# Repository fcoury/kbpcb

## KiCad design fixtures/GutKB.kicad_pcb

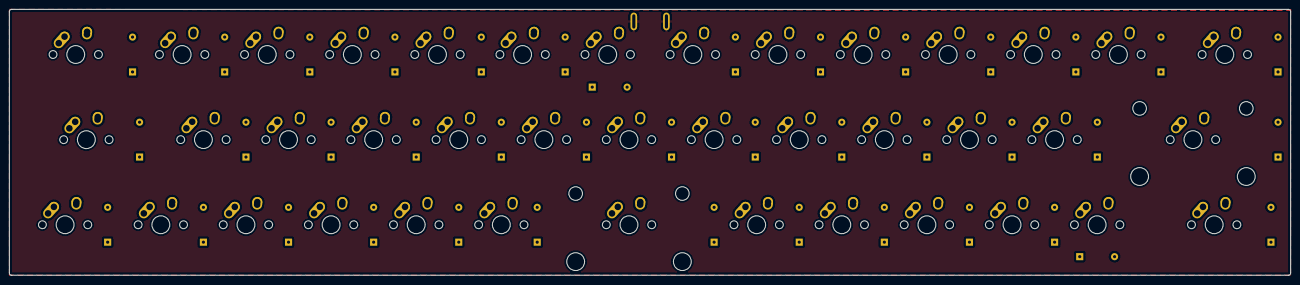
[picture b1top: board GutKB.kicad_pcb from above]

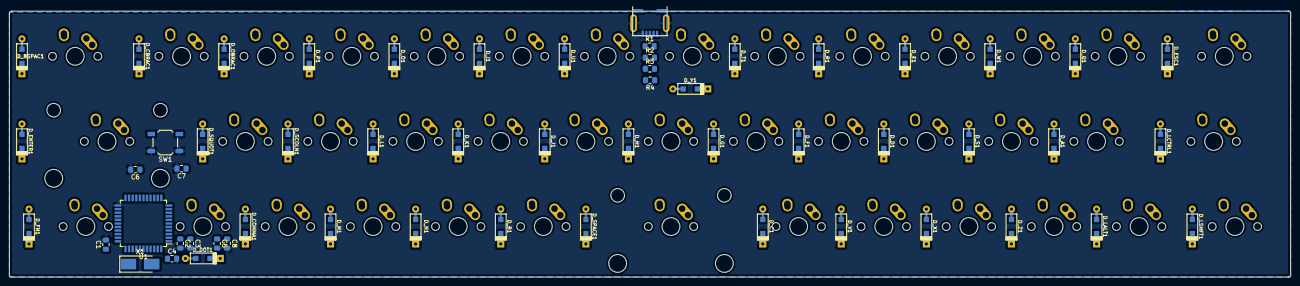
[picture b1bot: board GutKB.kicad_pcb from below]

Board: 2 copper layers, 286.8 x 59.5 mm, 96 parts (56 on the bottom side), 67 nets, no tracks yet.

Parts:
C1, C2: 22pF; C_0805_2012Metric_Pad1.15x1.40mm_HandSolder
C3, C4, C5, C6: 0.1u; C_0805_2012Metric_Pad1.15x1.40mm_HandSolder
C7: 4.7u; C_0805_2012Metric_Pad1.15x1.40mm_HandSolder
C8: 1u; C_0805_2012Metric_Pad1.15x1.40mm_HandSolder
D_A1: D; D_SOD123_axial
D_B1: D; D_SOD123_axial
D_BSPAC1: D; D_SOD123_axial
D_C1: D; D_SOD123_axial
D_CBRAC1: D; D_SOD123_axial
D_COMMA1: D; D_SOD123_axial
D_D1: D; D_SOD123_axial
D_DOT1: D; D_SOD123_axial
D_E1: D; D_SOD123_axial
D_ENTER1: D; D_SOD123_axial
D_ESC1: D; D_SOD123_axial
D_F1: D; D_SOD123_axial
D_FN1: D; D_SOD123_axial
D_G1: D; D_SOD123_axial
D_H1: D; D_SOD123_axial
D_I1: D; D_SOD123_axial
D_J1: D; D_SOD123_axial
D_K1: D; D_SOD123_axial
D_L1: D; D_SOD123_axial
D_LALT1: D; D_SOD123_axial
D_LCTRL1: D; D_SOD123_axial
D_LSHFT1: D; D_SOD123_axial
D_M1: D; D_SOD123_axial
D_N1: D; D_SOD123_axial
D_O1: D; D_SOD123_axial
D_OBRAC1: D; D_SOD123_axial
D_P1: D; D_SOD123_axial
D_Q1: D; D_SOD123_axial
D_R1: D; D_SOD123_axial
D_S1: D; D_SOD123_axial
D_SCOLN1: D; D_SOD123_axial
D_SPACE1: D; D_SOD123_axial
D_SQUOT1: D; D_SOD123_axial
D_T1: D; D_SOD123_axial
D_U1: D; D_SOD123_axial
D_V1: D; D_SOD123_axial
D_W1: D; D_SOD123_axial
D_X1: D; D_SOD123_axial
D_Y1: D; D_SOD123_axial
D_Z1: D; D_SOD123_axial
J1: USB_mini_micro_B; USB_miniB_hirose_5S8
K_A1: KEYSW; MX-1U-NoLED
K_B1: KEYSW; MX-1U-NoLED
K_BSPAC1: KEYSW; MX-1.5U-NoLED
K_C1: KEYSW; MX-1U-NoLED
K_CBRAC1: KEYSW; MX-1U-NoLED
K_COMMA1: KEYSW; MX-1U-NoLED
K_D1: KEYSW; MX-1U-NoLED
K_DOT1: KEYSW; MX-1U-NoLED
K_E1: KEYSW; MX-1U-NoLED
K_ENTER1: KEYSW; MX-2.25U-NoLED
K_ESC1: KEYSW; MX-1.5U-NoLED
K_F1: KEYSW; MX-1U-NoLED
K_FN1: KEYSW; MX-1.75U-NoLED
K_G1: KEYSW; MX-1U-NoLED
K_H1: KEYSW; MX-1U-NoLED
K_I1: KEYSW; MX-1U-NoLED
K_J1: KEYSW; MX-1U-NoLED
K_K1: KEYSW; MX-1U-NoLED
K_L1: KEYSW; MX-1U-NoLED
K_LALT1: KEYSW; MX-1U-NoLED
K_LCTRL1: KEYSW; MX-1.75U-NoLED
K_LSHFT1: KEYSW; MX-1.25U-NoLED
K_M1: KEYSW; MX-1U-NoLED
K_N1: KEYSW; MX-1U-NoLED
K_O1: KEYSW; MX-1U-NoLED
K_OBRAC1: KEYSW; MX-1U-NoLED
K_P1: KEYSW; MX-1U-NoLED
K_Q1: KEYSW; MX-1U-NoLED
K_R1: KEYSW; MX-1U-NoLED
K_S1: KEYSW; MX-1U-NoLED
K_SCOLN1: KEYSW; MX-1U-NoLED
K_SPACE1: KEYSW; MX-2U-NoLED
K_SQUOT1: KEYSW; MX-1U-NoLED
K_T1: KEYSW; MX-1U-NoLED
K_U1: KEYSW; MX-1U-NoLED
K_V1: KEYSW; MX-1U-NoLED
K_W1: KEYSW; MX-1U-NoLED
K_X1: KEYSW; MX-1U-NoLED
K_Y1: KEYSW; MX-1U-NoLED
K_Z1: KEYSW; MX-1U-NoLED
R1, R2: 10k; R_0805_2012Metric_Pad1.15x1.40mm_HandSolder
R3, R4: 22; R_0805_2012Metric_Pad1.15x1.40mm_HandSolder
SW1: SW_PUSH; SW_SPST_TL3342
U1: ATMEGA32U4; TQFP-44_10x10mm_P0.8mm
X1: XTAL_GND; Crystal_SMD_5032-2Pin_5.0x3.2mm_HandSoldering

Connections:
/Matrix/col0: K_ESC1.1, K_LCTRL1.1, K_LSHFT1.1
/Matrix/col1: K_A1.1, K_LALT1.1, K_Q1.1
/Matrix/col2: K_S1.1, K_W1.1, K_Z1.1
/Matrix/col3: K_D1.1, K_E1.1, K_X1.1
/Matrix/col4: K_C1.1, K_F1.1, K_R1.1
/Matrix/col5: K_G1.1, K_T1.1, K_V1.1
/Matrix/col6: K_H1.1, K_SPACE1.1, K_Y1.1
/Matrix/col7: K_B1.1, K_J1.1, K_U1.1
/Matrix/col8: K_I1.1, K_K1.1, K_N1.1
/Matrix/col9: K_L1.1, K_M1.1, K_O1.1
/Matrix/col10: K_COMMA1.1, K_P1.1, K_SCOLN1.1
/Matrix/col11: K_DOT1.1, K_OBRAC1.1, K_SQUOT1.1
/Matrix/col12: K_CBRAC1.1, K_ENTER1.1, K_FN1.1
/Matrix/row0: D_BSPAC1.1, D_CBRAC1.1, D_E1.1, D_ESC1.1, D_I1.1, D_O1.1, D_OBRAC1.1, D_P1.1, D_Q1.1, D_R1.1, D_T1.1, D_U1.1, D_W1.1, D_Y1.1
/Matrix/row1: D_A1.1, D_D1.1, D_ENTER1.1, D_F1.1, D_G1.1, D_H1.1, D_J1.1, D_K1.1, D_L1.1, D_LCTRL1.1, D_S1.1, D_SCOLN1.1, D_SQUOT1.1
/Matrix/row2: D_B1.1, D_C1.1, D_COMMA1.1, D_DOT1.1, D_FN1.1, D_LALT1.1, D_LSHFT1.1, D_M1.1, D_N1.1, D_SPACE1.1, D_V1.1, D_X1.1, D_Z1.1
GND: C1.2, C2.2, C3.2, C4.2, C5.2, C6.2, C7.2, C8.2, J1.5, J1.6, R2.1, SW1.1, U1.5, U1.15, U1.23
unnamed: C1.1, U1.16, X1.1
unnamed: C2.1, U1.17, X1.2
unnamed: C8.1, U1.6
unnamed: D_A1.2, K_A1.2
unnamed: D_B1.2, K_B1.2
unnamed: D_BSPAC1.2, K_BSPAC1.2
unnamed: D_C1.2, K_C1.2
unnamed: D_CBRAC1.2, K_CBRAC1.2
unnamed: D_COMMA1.2, K_COMMA1.2
unnamed: D_D1.2, K_D1.2
unnamed: D_DOT1.2, K_DOT1.2
unnamed: D_E1.2, K_E1.2
unnamed: D_ENTER1.2, K_ENTER1.2
unnamed: D_ESC1.2, K_ESC1.2
unnamed: D_F1.2, K_F1.2
unnamed: D_FN1.2, K_FN1.2
unnamed: D_G1.2, K_G1.2
unnamed: D_H1.2, K_H1.2
unnamed: D_I1.2, K_I1.2
unnamed: D_J1.2, K_J1.2
unnamed: D_K1.2, K_K1.2
unnamed: D_L1.2, K_L1.2
unnamed: D_LALT1.2, K_LALT1.2
unnamed: D_LCTRL1.2, K_LCTRL1.2
unnamed: D_LSHFT1.2, K_LSHFT1.2
unnamed: D_M1.2, K_M1.2
unnamed: D_N1.2, K_N1.2
unnamed: D_O1.2, K_O1.2
unnamed: D_OBRAC1.2, K_OBRAC1.2
unnamed: D_P1.2, K_P1.2
unnamed: D_Q1.2, K_Q1.2
unnamed: D_R1.2, K_R1.2
unnamed: D_S1.2, K_S1.2
unnamed: D_SCOLN1.2, K_SCOLN1.2
unnamed: D_SPACE1.2, K_SPACE1.2
unnamed: D_SQUOT1.2, K_SQUOT1.2
unnamed: D_T1.2, K_T1.2
unnamed: D_U1.2, K_U1.2
unnamed: D_V1.2, K_V1.2
unnamed: D_W1.2, K_W1.2
unnamed: D_X1.2, K_X1.2
unnamed: D_Y1.2, K_Y1.2
unnamed: D_Z1.2, K_Z1.2
unnamed: J1.2, R3.2
unnamed: J1.3, R4.2
unnamed: R1.1, SW1.2, U1.13
unnamed: R2.2, U1.33
unnamed: R3.1, U1.3
unnamed: R4.1, U1.4
VCC: C3.1, C4.1, C5.1, C6.1, C7.1, J1.1, R1.2, U1.2, U1.14, U1.24

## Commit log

2019-03-08 chore: initial commit
2019-03-08 feat: switches and diodes schematics work
2019-03-08 feat: complete matrix being drawn
2019-03-08 chore: added footprint library
2019-03-08 chore: added new layout examples
2019-03-08 refactor: extracted Schematics class
2019-03-08 feat: initial PCB design support
2019-03-09 feat: serves PCB design and schematics over HTTP
2019-03-09 fix: npm start command for heroku
2019-03-09 fix: handles backslash as key name
2019-03-09 chore: uses uploaded file name if no name is given
2019-03-09 chore: removed name from form
2019-03-09 feat: adds PCB border and USB port
2019-03-09 feat: new layout
2019-03-09 feat: added Google Analytics
2019-03-09 chore: added link to YouTube demo
2019-03-10 feat: initial rotation support
2019-03-10 feat: added height support
2019-03-10 feat: produces a feature complete zip with all the dependencies
2019-03-10 chore: removed MX_Alps library
2019-03-10 feat: readied MX_Alps library
2019-03-10 fix: sym-lib-table contents
2019-03-10 feat: add footprints and initial error handling
2019-03-10 feat: uses GLabel for the matrix schematics
2019-03-10 fix: properly calculate width even if last switch is not 1u
2019-03-10 feat: added main PCB schematics
2019-03-10 feat: adds VCC and GND planes
2019-03-11 feat: added additional components to the PCB
2019-03-11 feat: microprocessor wiring
2019-03-11 feat: added more connections
2019-03-11 feat: initial refactoring
2019-03-11 feat: component and net repository initial implementation
2019-03-11 feat: PCB generation working for diodes and switches
2019-03-11 feat: connections between switches, diodes and rows
2019-03-11 feat: initial plane support
2019-03-12 feat: added Frame and gaps
2019-03-12 feat: microcontroller initial connections
2019-03-12 feat: added reset button
2019-03-12 feat: schematics
2019-03-12 feat: validate key names
2019-03-12 feat: added more schematics connections
2019-03-12 feat: generate schematics with correct name for diodes
2019-03-12 fix: tests and web server working with refactoring
2019-03-12 chore: cleanup
2019-03-13 fix: uses correct switch name
2019-03-13 fix: rotates diode and its pads
2019-03-13 fix: proper rotation to all components
2019-03-13 feat: uses LED footprint for switches for the time being
2019-03-13 feat: made switch LED more flexible
2019-03-13 feat: allows selecting in-switch LEDs or not
2019-03-13 feat: renders PCB with initial X,Y coordinates
2019-03-13 feat: renders schematics with initial X,Y coordinates
2019-03-13 feat: major reorganization of source code
2019-03-13 feat: client side initial commit
2019-03-13 feat(cli): layout uploader, parser and editor
2019-05-31 docs: added MIT license. Closes #1
2019-11-02 chore(deps): bump mixin-deep from 1.3.1 to 1.3.2
    Bumps [mixin-deep](https://github.com/jonschlinkert/mixin-deep) from 1.3.1 to 1.3.2.
    - [Release notes](https://github.com/jonschlinkert/mixin-deep/releases)
    - [Commits](https://github.com/jonschlinkert/mixin-deep/compare/1.3.1...1.3.2)
2020-03-14 chore(deps): bump acorn from 6.1.1 to 6.4.1
    Bumps [acorn](https://github.com/acornjs/acorn) from 6.1.1 to 6.4.1.
    - [Release notes](https://github.com/acornjs/acorn/releases)
    - [Commits](https://github.com/acornjs/acorn/compare/6.1.1...6.4.1)
2020-04-11 All caps on lib table causes errors on lib linking on KiCAD side
2020-04-11 Added idea files to gitignore
2020-04-11 Special characters breaks the eeschema annotations
2020-04-11 Pre-adding numbers to end of the key definitions to fix annotation problems.
2020-04-11 Zip was putting libs stuff into wrong path
2020-04-11 Changed annotations to numbering eliminate complicated annotation clashes.
2020-06-03 chore: added warning that pcb isn't valid
2020-06-03 chore(deps): bump lodash from 4.17.11 to 4.17.15
    Bumps [lodash](https://github.com/lodash/lodash) from 4.17.11 to 4.17.15.
    - [Release notes](https://github.com/lodash/lodash/releases)
    - [Commits](https://github.com/lodash/lodash/compare/4.17.11...4.17.15)
2020-06-23 chore: added GitHub Code Analysis
2020-07-16 chore(deps): bump lodash from 4.17.15 to 4.17.19
    Bumps [lodash](https://github.com/lodash/lodash) from 4.17.15 to 4.17.19.
    - [Release notes](https://github.com/lodash/lodash/releases)
    - [Commits](https://github.com/lodash/lodash/compare/4.17.15...4.17.19)
2020-12-11 chore(deps): bump ini from 1.3.5 to 1.3.7
    Bumps [ini](https://github.com/isaacs/ini) from 1.3.5 to 1.3.7.
    - [Release notes](https://github.com/isaacs/ini/releases)
    - [Commits](https://github.com/isaacs/ini/compare/v1.3.5...v1.3.7)
2021-03-30 chore(deps): bump y18n from 3.2.1 to 3.2.2
    Bumps [y18n](https://github.com/yargs/y18n) from 3.2.1 to 3.2.2.
    - [Release notes](https://github.com/yargs/y18n/releases)
    - [Changelog](https://github.com/yargs/y18n/blob/master/CHANGELOG.md)
    - [Commits](https://github.com/yargs/y18n/commits)
2021-05-08 chore(deps): bump lodash from 4.17.15 to 4.17.21
    Bumps [lodash](https://github.com/lodash/lodash) from 4.17.15 to 4.17.21.
    - [Release notes](https://github.com/lodash/lodash/releases)
    - [Commits](https://github.com/lodash/lodash/compare/4.17.15...4.17.21)
2021-05-10 chore(deps): bump hosted-git-info from 2.7.1 to 2.8.9
    Bumps [hosted-git-info](https://github.com/npm/hosted-git-info) from 2.7.1 to 2.8.9.
    - [Release notes](https://github.com/npm/hosted-git-info/releases)
    - [Changelog](https://github.com/npm/hosted-git-info/blob/v2.8.9/CHANGELOG.md)
    - [Commits](https://github.com/npm/hosted-git-info/compare/v2.7.1...v2.8.9)
2021-08-03 chore(deps): bump tar from 4.4.8 to 4.4.15
    Bumps [tar](https://github.com/npm/node-tar) from 4.4.8 to 4.4.15.
    - [Release notes](https://github.com/npm/node-tar/releases)
    - [Changelog](https://github.com/npm/node-tar/blob/main/CHANGELOG.md)
    - [Commits](https://github.com/npm/node-tar/compare/v4.4.8...v4.4.15)
    ---
    updated-dependencies:
2021-08-10 chore(deps): bump path-parse from 1.0.6 to 1.0.7
    Bumps [path-parse](https://github.com/jbgutierrez/path-parse) from 1.0.6 to 1.0.7.
    - [Release notes](https://github.com/jbgutierrez/path-parse/releases)
    - [Commits](https://github.com/jbgutierrez/path-parse/commits/v1.0.7)
    ---
    updated-dependencies:
    - dependency-name: path-parse
2021-09-01 chore(deps): bump tar from 4.4.8 to 4.4.19
    Bumps [tar](https://github.com/npm/node-tar) from 4.4.8 to 4.4.19.
    - [Release notes](https://github.com/npm/node-tar/releases)
    - [Changelog](https://github.com/npm/node-tar/blob/main/CHANGELOG.md)
    - [Commits](https://github.com/npm/node-tar/compare/v4.4.8...v4.4.19)
    ---
    updated-dependencies:
2022-02-10 chore(deps): bump undefsafe from 2.0.2 to 2.0.5
    Bumps [undefsafe](https://github.com/remy/undefsafe) from 2.0.2 to 2.0.5.
    - [Release notes](https://github.com/remy/undefsafe/releases)
    - [Commits](https://github.com/remy/undefsafe/compare/v2.0.2...v2.0.5)
    ---
    updated-dependencies:
    - dependency-name: undefsafe
2022-02-11 chore(deps): bump pathval from 1.1.0 to 1.1.1
    Bumps [pathval](https://github.com/chaijs/pathval) from 1.1.0 to 1.1.1.
    - [Release notes](https://github.com/chaijs/pathval/releases)
    - [Changelog](https://github.com/chaijs/pathval/blob/master/CHANGELOG.md)
    - [Commits](https://github.com/chaijs/pathval/compare/v1.1.0...v1.1.1)
    ---
    updated-dependencies:
2022-09-08 chore(deps): bump jszip from 3.2.0 to 3.7.0
    Bumps [jszip](https://github.com/Stuk/jszip) from 3.2.0 to 3.7.0.
    - [Release notes](https://github.com/Stuk/jszip/releases)
    - [Changelog](https://github.com/Stuk/jszip/blob/main/CHANGES.md)
    - [Commits](https://github.com/Stuk/jszip/compare/v3.2.0...v3.7.0)
    ---
    updated-dependencies:
2022-12-03 chore(deps): bump decode-uri-component from 0.2.0 to 0.2.2
    Bumps [decode-uri-component](https://github.com/SamVerschueren/decode-uri-component) from 0.2.0 to 0.2.2.
    - [Release notes](https://github.com/SamVerschueren/decode-uri-component/releases)
    - [Commits](https://github.com/SamVerschueren/decode-uri-component/compare/v0.2.0...v0.2.2)
    ---
    updated-dependencies:
    - dependency-name: decode-uri-component
2022-12-09 chore(deps): bump express from 4.16.4 to 4.17.3
    Bumps [express](https://github.com/expressjs/express) from 4.16.4 to 4.17.3.
    - [Release notes](https://github.com/expressjs/express/releases)
    - [Changelog](https://github.com/expressjs/express/blob/master/History.md)
    - [Commits](https://github.com/expressjs/express/compare/4.16.4...4.17.3)
    ---
    updated-dependencies:
